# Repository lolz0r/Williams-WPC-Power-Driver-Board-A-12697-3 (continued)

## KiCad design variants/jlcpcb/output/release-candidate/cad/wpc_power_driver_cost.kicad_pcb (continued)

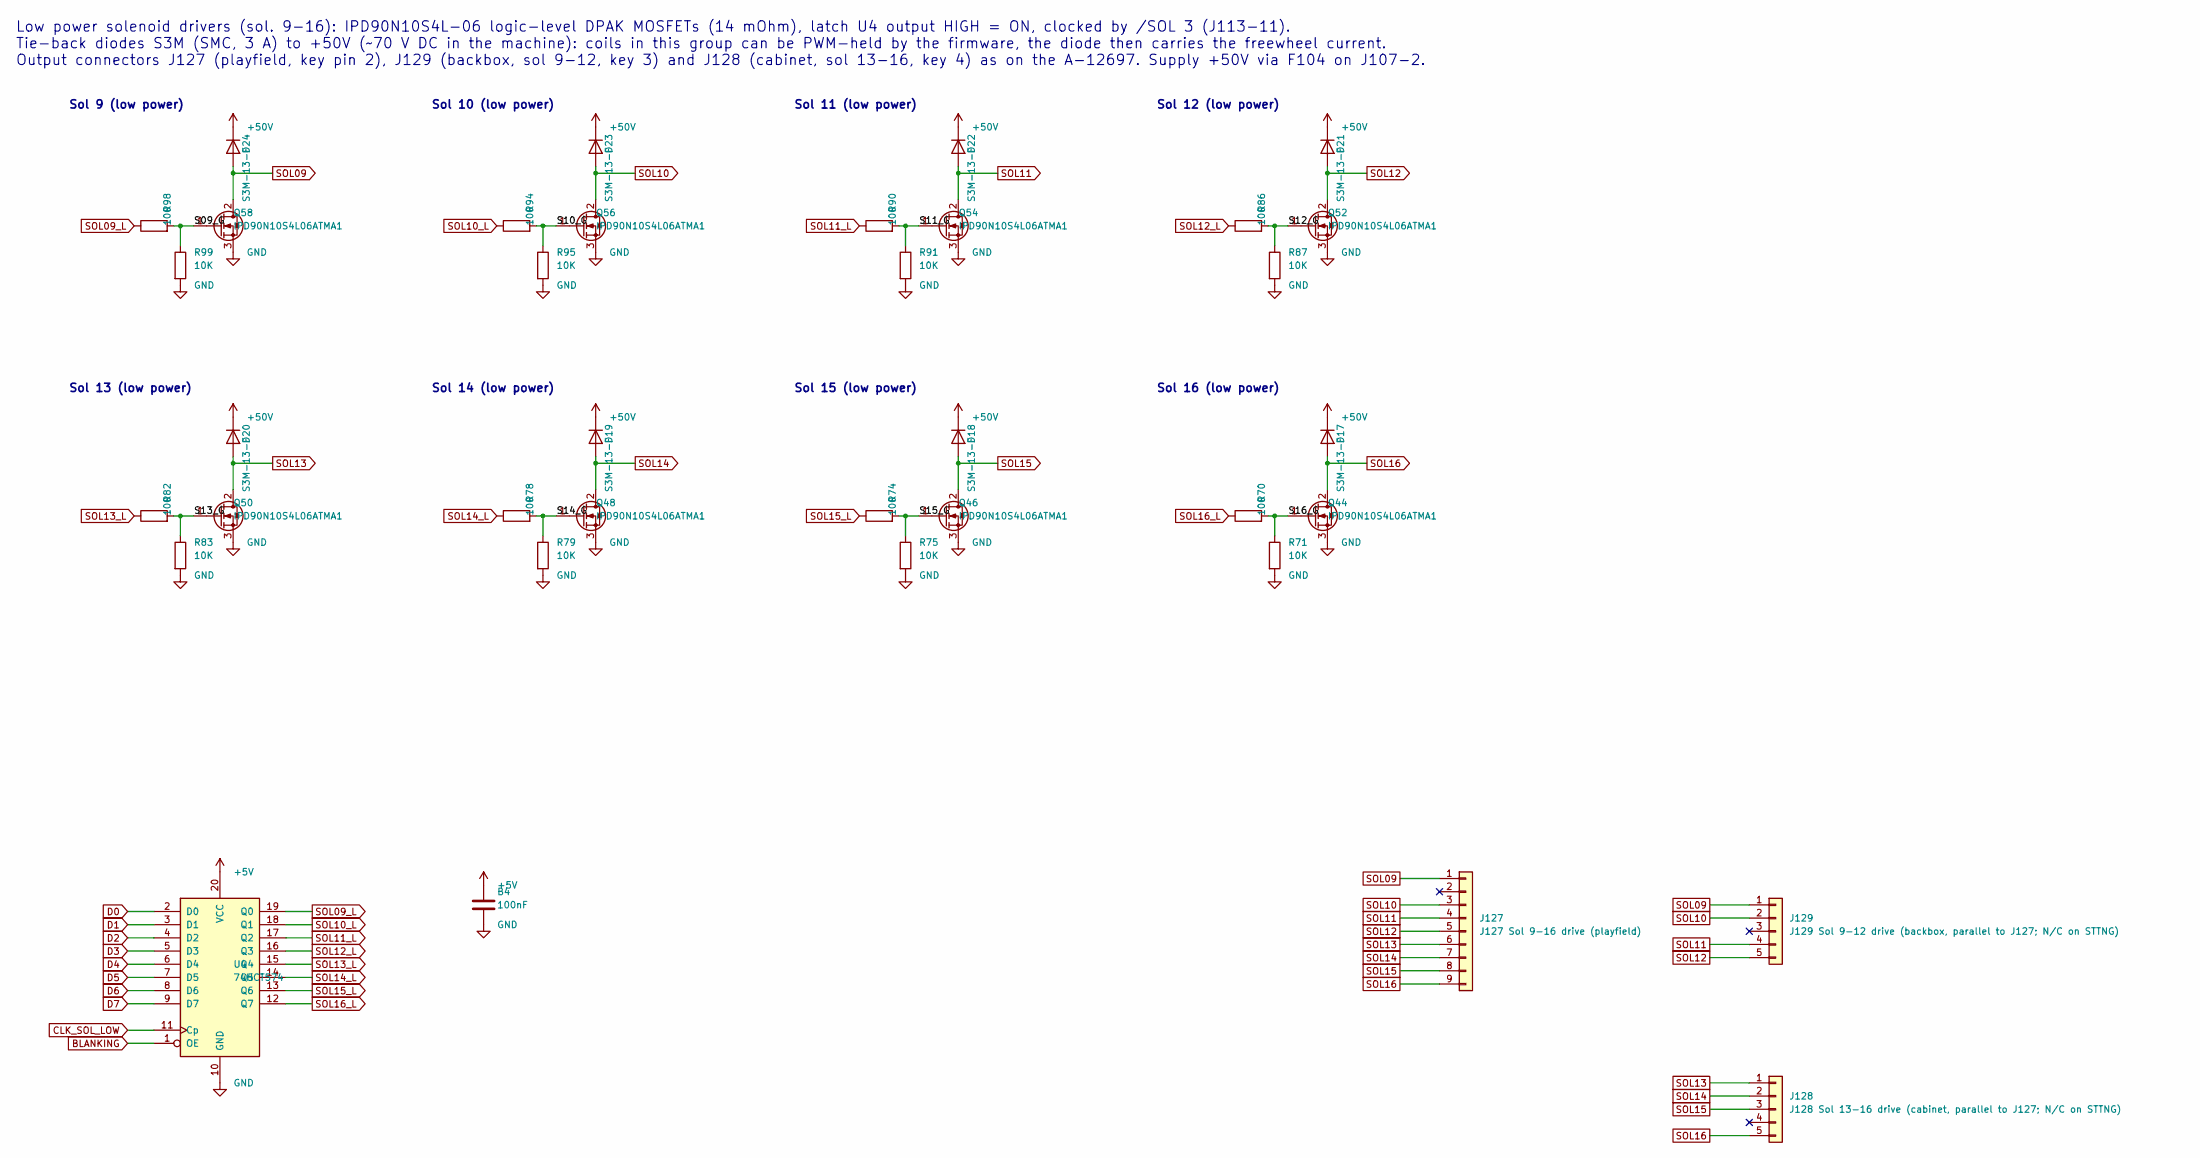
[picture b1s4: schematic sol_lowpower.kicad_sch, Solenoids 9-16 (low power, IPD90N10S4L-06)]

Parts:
B4: 100nF; C_0805_2012Metric; MPN CC0805KRX7R9BB104; JLCPCB Part C49678
D17, D18, D19, D20, D21, D22, D23, D24: S3M-13-F; D_SMC; MPN S3M-13-F; JLCPCB Part C460944
J127: J127 Sol 9-16 drive (playfield); Molex_KK-396_A-41791-0009_1x09_P3.96mm_Vertical; MPN 0026604090; JLCPCB Part C17420444
J128: J128 Sol 13-16 drive (cabinet, parallel to J127; 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; Molex_KK-396_A-41791-0005_1x05_P3.96mm_Vertical; MPN 26604050; JLCPCB Part C505166
J129: J129 Sol 9-12 drive (backbox, parallel to J127; N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; Molex_KK-396_A-41791-0005_1x05_P3.96mm_Vertical; MPN 26604050; JLCPCB Part C505166
Q44, Q46, Q48, Q50, Q52, Q54, Q56, Q58: IPD90N10S4L06ATMA1; TO-252-2; MPN IPD90N10S4L06ATMA1; JLCPCB Part C5440942
R70, R74, R78, R82, R86, R90, R94, R98: 100; R_0805_2012Metric; MPN 0805W8F1000T5E; JLCPCB Part C17408
R71, R75, R79, R83, R87, R91, R95, R99: 10K; R_0805_2012Metric; MPN 0805W8F1002T5E; JLCPCB Part C17414
U4: 74HCT574; SOIC-20W_7.5x12.8mm_P1.27mm; MPN SN74HCT574DWR; JLCPCB Part C6788

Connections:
+5V: B4.1, U4.20 (VCC); also elsewhere on the board
+50V: D17.1 (K), D18.1 (K), D19.1 (K), D20.1 (K), D21.1 (K), D22.1 (K), D23.1 (K), D24.1 (K); also elsewhere on the board
/Sol_LowPower/S09_G: Q58.1 (G), R98.2, R99.1
/Sol_LowPower/S10_G: Q56.1 (G), R94.2, R95.1
/Sol_LowPower/S11_G: Q54.1 (G), R90.2, R91.1
/Sol_LowPower/S12_G: Q52.1 (G), R86.2, R87.1
/Sol_LowPower/S13_G: Q50.1 (G), R82.2, R83.1
/Sol_LowPower/S14_G: Q48.1 (G), R78.2, R79.1
/Sol_LowPower/S15_G: Q46.1 (G), R74.2, R75.1
/Sol_LowPower/S16_G: Q44.1 (G), R70.2, R71.1
BLANKING: U4.1 (OE); also elsewhere on the board
CLK_SOL_LOW: U4.11 (Cp); also elsewhere on the board
D0: U4.2 (D0); also elsewhere on the board
D1: U4.3 (D1); also elsewhere on the board
D2: U4.4 (D2); also elsewhere on the board
D3: U4.5 (D3); also elsewhere on the board
D4: U4.6 (D4); also elsewhere on the board
D5: U4.7 (D5); also elsewhere on the board
D6: U4.8 (D6); also elsewhere on the board
D7: U4.9 (D7); also elsewhere on the board
SOL09: D24.2 (A), J127.1, J129.1, Q58.2 (D)
SOL09_L: R98.1, U4.19 (Q0)
SOL10: D23.2 (A), J127.3, J129.2, Q56.2 (D)
SOL10_L: R94.1, U4.18 (Q1)
SOL11: D22.2 (A), J127.4, J129.4, Q54.2 (D)
SOL11_L: R90.1, U4.17 (Q2)
SOL12: D21.2 (A), J127.5, J129.5, Q52.2 (D)
SOL12_L: R86.1, U4.16 (Q3)
SOL13: D20.2 (A), J127.6, J128.1, Q50.2 (D)
SOL13_L: R82.1, U4.15 (Q4)
SOL14: D19.2 (A), J127.7, J128.2, Q48.2 (D)
SOL14_L: R78.1, U4.14 (Q5)
SOL15: D18.2 (A), J127.8, J128.3, Q46.2 (D)
SOL15_L: R74.1, U4.13 (Q6)
SOL16: D17.2 (A), J127.9, J128.5, Q44.2 (D)
SOL16_L: R70.1, U4.12 (Q7)

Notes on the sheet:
Sol 9 (low power)
Sol 10 (low power)
Sol 11 (low power)
Sol 12 (low power)
Sol 13 (low power)
Sol 14 (low power)
Sol 15 (low power)
Sol 16 (low power)
Low power solenoid drivers (sol. 9-16): IPD90N10S4L-06 logic-level DPAK MOSFETs (14 mOhm), latch U4 output HIGH = ON, clocked by /SOL 3 (J113-11). Tie-back diodes S3M (SMC, 3 A) to +50V (~70 V DC in the machine): coils in this group can be PWM-held by the firmware, the diode then carries the freewh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

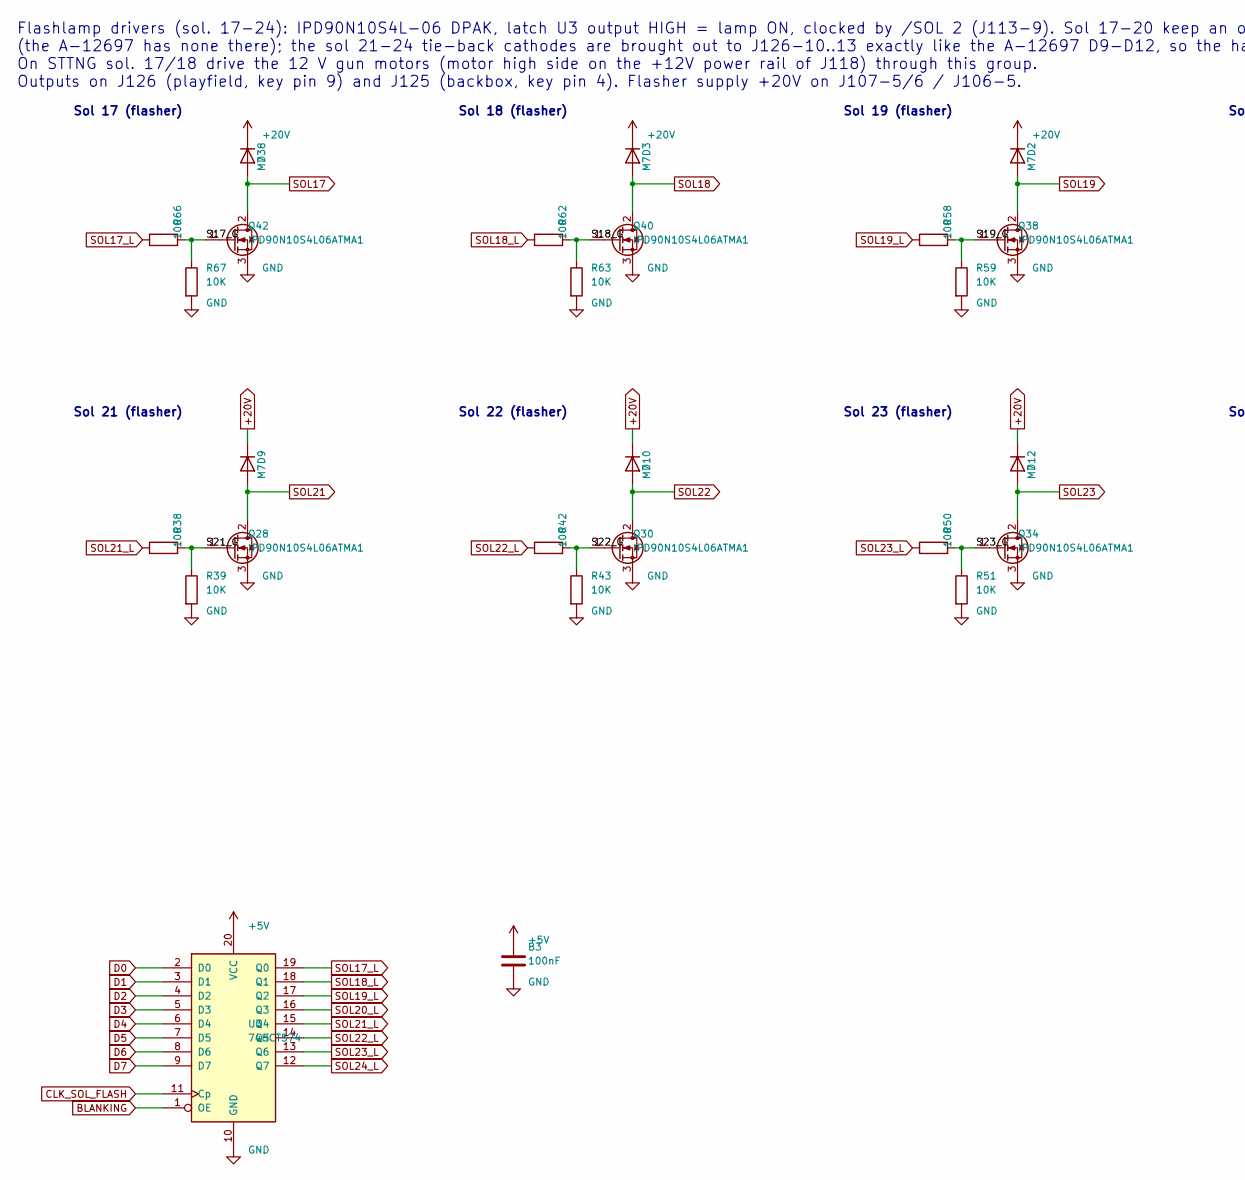
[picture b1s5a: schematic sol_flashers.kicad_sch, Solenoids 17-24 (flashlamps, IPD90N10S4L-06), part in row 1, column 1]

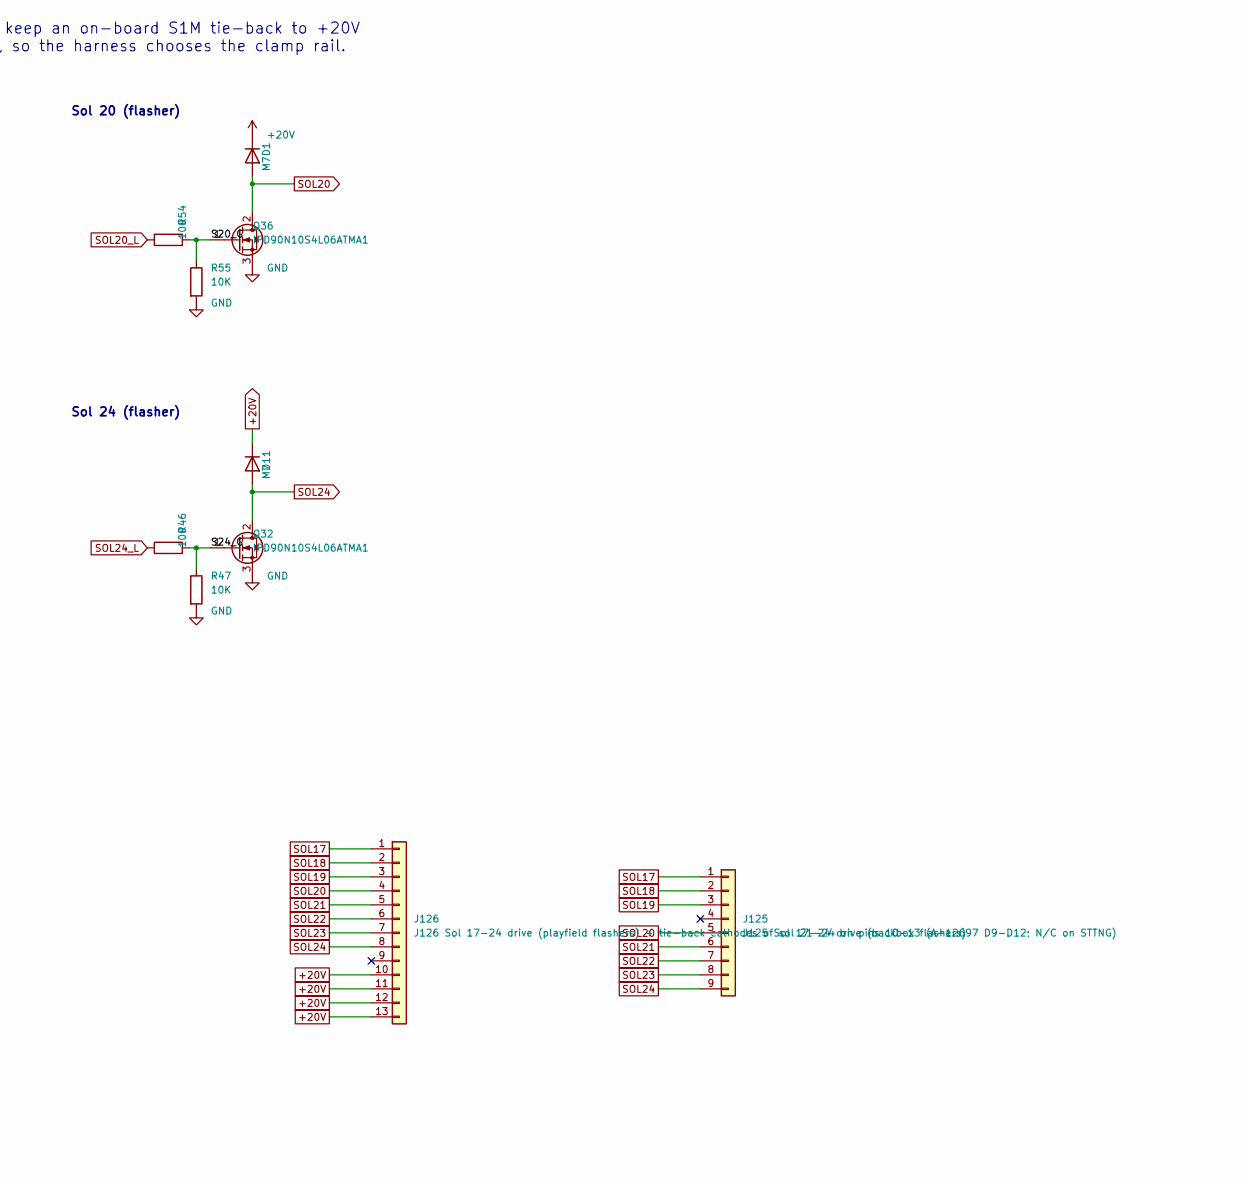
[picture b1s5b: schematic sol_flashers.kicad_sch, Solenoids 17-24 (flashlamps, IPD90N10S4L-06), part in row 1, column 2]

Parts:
B3: 100nF; C_0805_2012Metric; MPN CC0805KRX7R9BB104; JLCPCB Part C49678
D1, D2, D3, D9, D10, D11, D12, D38: M7; D_SMA; MPN M7; JLCPCB Part C95872
J125: J125 Sol 17-24 drive (backbox flashers); Molex_KK-396_A-41791-0009_1x09_P3.96mm_Vertical; MPN 0026604090; JLCPCB Part C17420444
J126: J126 Sol 17-24 drive (playfield flashers) + tie-b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; Molex_KK-396_A-41791-0013_1x13_P3.96mm_Vertical; MPN 0026604130; JLCPCB Part C17226055
Q28, Q30, Q32, Q34, Q36, Q38, Q40, Q42: IPD90N10S4L06ATMA1; TO-252-2; MPN IPD90N10S4L06ATMA1; JLCPCB Part C5440942
R38, R42, R46, R50, R54, R58, R62, R66: 100; R_0805_2012Metric; MPN 0805W8F1000T5E; JLCPCB Part C17408
R39, R43, R47, R51, R55, R59, R63, R67: 10K; R_0805_2012Metric; MPN 0805W8F1002T5E; JLCPCB Part C17414
U3: 74HCT574; SOIC-20W_7.5x12.8mm_P1.27mm; MPN SN74HCT574DWR; JLCPCB Part C6788

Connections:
+5V: B3.1, U3.20 (VCC); also elsewhere on the board
+20V: D1.1 (K), D2.1 (K), D3.1 (K), D9.1 (K), D10.1 (K), D11.1 (K), D12.1 (K), D38.1 (K), J126.10, J126.11, J126.12, J126.13; also elsewhere on the board
/Sol_Flashers/S17_G: Q42.1 (G), R66.2, R67.1
/Sol_Flashers/S18_G: Q40.1 (G), R62.2, R63.1
/Sol_Flashers/S19_G: Q38.1 (G), R58.2, R59.1
/Sol_Flashers/S20_G: Q36.1 (G), R54.2, R55.1
/Sol_Flashers/S21_G: Q28.1 (G), R38.2, R39.1
/Sol_Flashers/S22_G: Q30.1 (G), R42.2, R43.1
/Sol_Flashers/S23_G: Q34.1 (G), R50.2, R51.1
/Sol_Flashers/S24_G: Q32.1 (G), R46.2, R47.1
BLANKING: U3.1 (OE); also elsewhere on the board
CLK_SOL_FLASH: U3.11 (Cp); also elsewhere on the board
D0: U3.2 (D0); also elsewhere on the board
D1: U3.3 (D1); also elsewhere on the board
D2: U3.4 (D2); also elsewhere on the board
D3: U3.5 (D3); also elsewhere on the board
D4: U3.6 (D4); also elsewhere on the board
D5: U3.7 (D5); also elsewhere on the board
D6: U3.8 (D6); also elsewhere on the board
D7: U3.9 (D7); also elsewhere on the board
SOL17: D38.2 (A), J125.1, J126.1, Q42.2 (D)
SOL17_L: R66.1, U3.19 (Q0)
SOL18: D3.2 (A), J125.2, J126.2, Q40.2 (D)
SOL18_L: R62.1, U3.18 (Q1)
SOL19: D2.2 (A), J125.3, J126.3, Q38.2 (D)
SOL19_L: R58.1, U3.17 (Q2)
SOL20: D1.2 (A), J125.5, J126.4, Q36.2 (D)
SOL20_L: R54.1, U3.16 (Q3)
SOL21: D9.2 (A), J125.6, J126.5, Q28.2 (D)
SOL21_L: R38.1, U3.15 (Q4)
SOL22: D10.2 (A), J125.7, J126.6, Q30.2 (D)
SOL22_L: R42.1, U3.14 (Q5)
SOL23: D12.2 (A), J125.8, J126.7, Q34.2 (D)
SOL23_L: R50.1, U3.13 (Q6)
SOL24: D11.2 (A), J125.9, J126.8, Q32.2 (D)
SOL24_L: R46.1, U3.12 (Q7)

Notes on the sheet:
Sol 17 (flasher)
Sol 18 (flasher)
Sol 19 (flasher)
Sol 20 (flasher)
Sol 21 (flasher)
Sol 22 (flasher)
Sol 23 (flasher)
Sol 24 (flasher)
Flashlamp drivers (sol. 17-24): IPD90N10S4L-06 DPAK, latch U3 output HIGH = lamp ON, clocked by /SOL 2 (J113-9). Sol 17-20 keep an on-board S1M tie-back to +20V (the A-12697 has none there); the sol 21-24 tie-back cathodes are brought out to J126-10..13 exactly like the A-12697 D9-D12, so the harne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

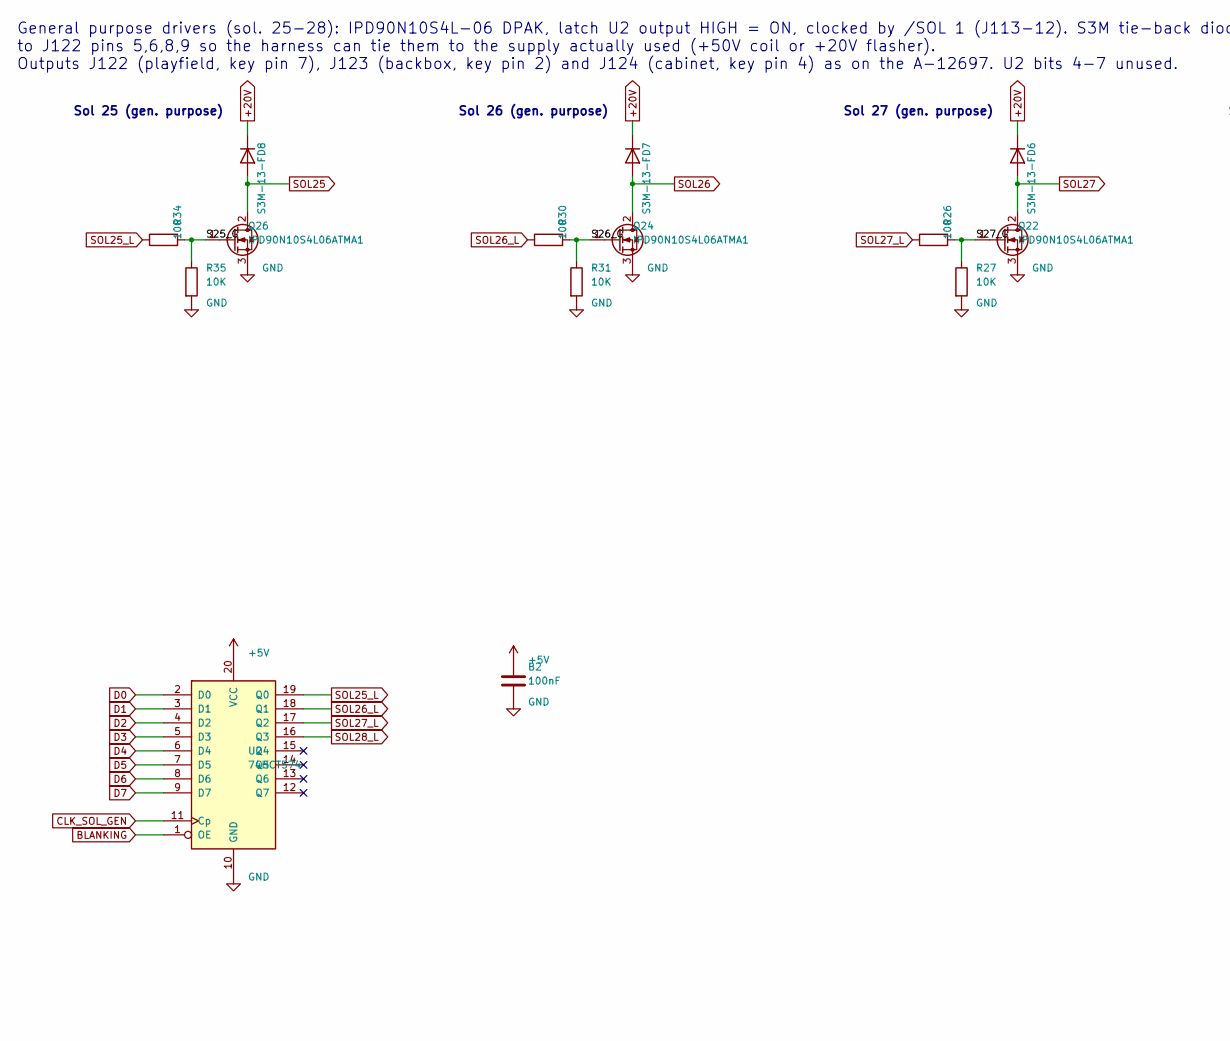
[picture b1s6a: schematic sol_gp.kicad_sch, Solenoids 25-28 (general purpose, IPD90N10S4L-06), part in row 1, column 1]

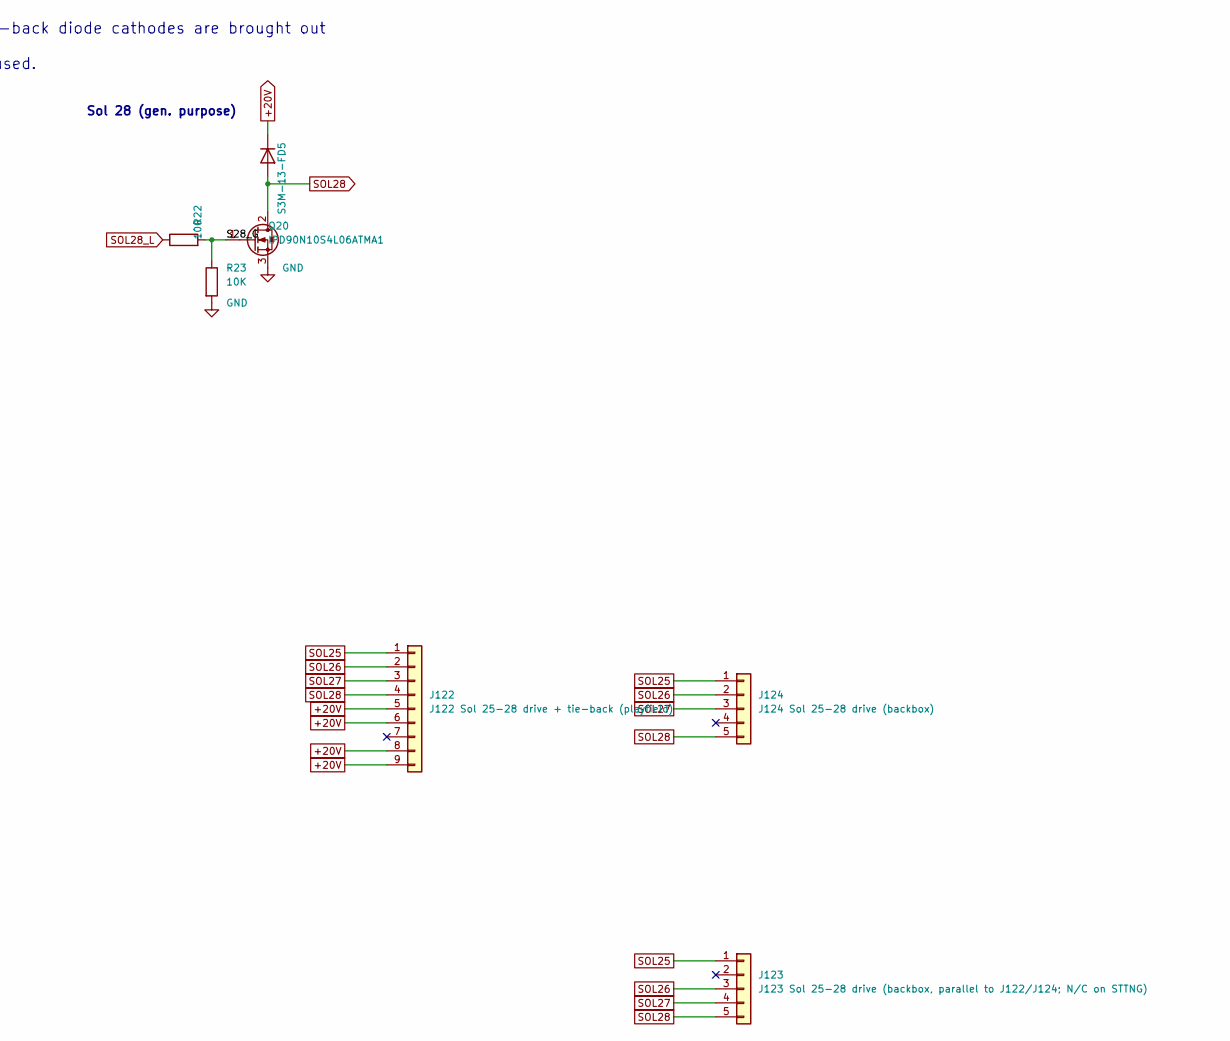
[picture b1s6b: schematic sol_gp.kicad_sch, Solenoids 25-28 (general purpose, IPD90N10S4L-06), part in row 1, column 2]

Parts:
B2: 100nF; C_0805_2012Metric; MPN CC0805KRX7R9BB104; JLCPCB Part C49678
D5, D6, D7, D8: S3M-13-F; D_SMC; MPN S3M-13-F; JLCPCB Part C460944
J122: J122 Sol 25-28 drive + tie-back (playfield); Molex_KK-396_A-41791-0009_1x09_P3.96mm_Vertical; MPN 0026604090; JLCPCB Part C17420444
J123: J123 Sol 25-28 drive (backbox, parallel to J122/J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; Molex_KK-396_A-41791-0005_1x05_P3.96mm_Vertical; MPN 26604050; JLCPCB Part C505166
J124: J124 Sol 25-28 drive (backbox); Molex_KK-396_A-41791-0005_1x05_P3.96mm_Vertical; MPN 26604050; JLCPCB Part C505166
Q20, Q22, Q24, Q26: IPD90N10S4L06ATMA1; TO-252-2; MPN IPD90N10S4L06ATMA1; JLCPCB Part C5440942
R22, R26, R30, R34: 100; R_0805_2012Metric; MPN 0805W8F1000T5E; JLCPCB Part C17408
R23, R27, R31, R35: 10K; R_0805_2012Metric; MPN 0805W8F1002T5E; JLCPCB Part C17414
U2: 74HCT574; SOIC-20W_7.5x12.8mm_P1.27mm; MPN SN74HCT574DWR; JLCPCB Part C6788

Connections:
+5V: B2.1, U2.20 (VCC); also elsewhere on the board
+20V: D5.1 (K), D6.1 (K), D7.1 (K), D8.1 (K), J122.5, J122.6, J122.8, J122.9; also elsewhere on the board
/Sol_GeneralPurpose/S25_G: Q26.1 (G), R34.2, R35.1
/Sol_GeneralPurpose/S26_G: Q24.1 (G), R30.2, R31.1
/Sol_GeneralPurpose/S27_G: Q22.1 (G), R26.2, R27.1
/Sol_GeneralPurpose/S28_G: Q20.1 (G), R22.2, R23.1
BLANKING: U2.1 (OE); also elsewhere on the board
CLK_SOL_GEN: U2.11 (Cp); also elsewhere on the board
D0: U2.2 (D0); also elsewhere on the board
D1: U2.3 (D1); also elsewhere on the board
D2: U2.4 (D2); also elsewhere on the board
D3: U2.5 (D3); also elsewhere on the board
D4: U2.6 (D4); also elsewhere on the board
D5: U2.7 (D5); also elsewhere on the board
D6: U2.8 (D6); also elsewhere on the board
D7: U2.9 (D7); also elsewhere on the board
SOL25: D8.2 (A), J122.1, J123.1, J124.1, Q26.2 (D)
SOL25_L: R34.1, U2.19 (Q0)
SOL26: D7.2 (A), J122.2, J123.3, J124.2, Q24.2 (D)
SOL26_L: R30.1, U2.18 (Q1)
SOL27: D6.2 (A), J122.3, J123.4, J124.3, Q22.2 (D)
SOL27_L: R26.1, U2.17 (Q2)
SOL28: D5.2 (A), J122.4, J123.5, J124.5, Q20.2 (D)
SOL28_L: R22.1, U2.16 (Q3)

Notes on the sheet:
Sol 25 (gen. purpose)
Sol 26 (gen. purpose)
Sol 27 (gen. purpose)
Sol 28 (gen. purpose)
General purpose drivers (sol. 25-28): IPD90N10S4L-06 DPAK, latch U2 output HIGH = ON, clocked by /SOL 1 (J113-12). S3M tie-back diode cathodes are brought out to J122 pins 5,6,8,9 so the harness can tie them to the supply actually used (+50V coil or +20V flasher). Outputs J122 (playfield, key pin 7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

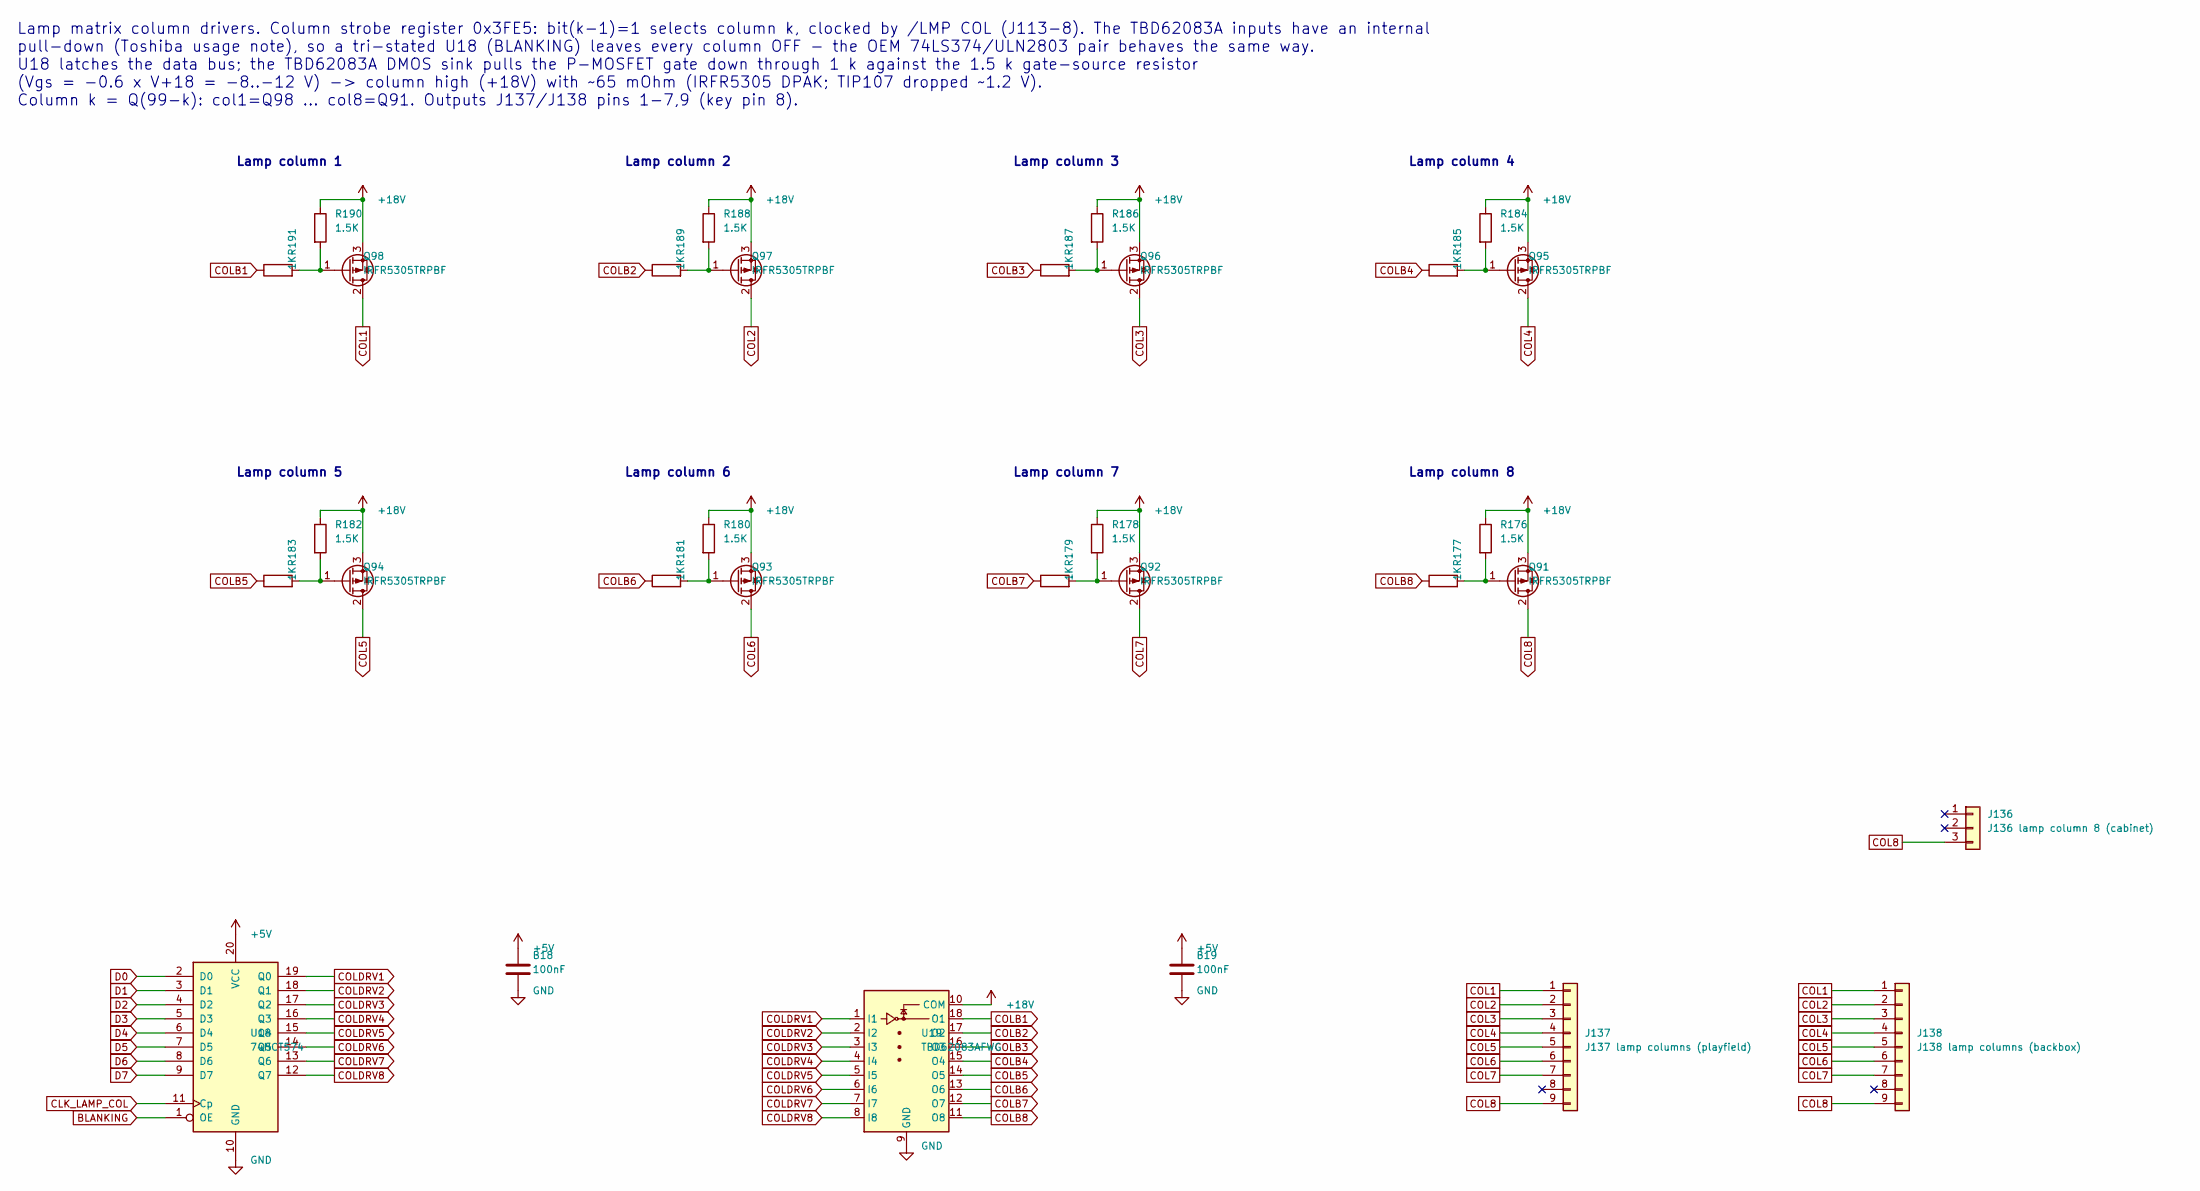
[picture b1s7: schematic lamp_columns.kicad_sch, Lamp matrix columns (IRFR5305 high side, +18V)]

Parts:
B18, B19: 100nF; C_0805_2012Metric; MPN CC0805KRX7R9BB104; JLCPCB Part C49678
J136: J136 lamp column 8 (cabinet); Molex_KK-396_A-41791-0003_1x03_P3.96mm_Vertical; MPN 26604030; JLCPCB Part C240823
J137: J137 lamp columns (playfield); Molex_KK-396_A-41791-0009_1x09_P3.96mm_Vertical; MPN 0026604090; JLCPCB Part C17420444
J138: J138 lamp columns (backbox); Molex_KK-396_A-41791-0009_1x09_P3.96mm_Vertical; MPN 0026604090; JLCPCB Part C17420444
Q91, Q92, Q93, Q94, Q95, Q96, Q97, Q98: IRFR5305TRPBF; TO-252-2; MPN IRFR5305TRPBF; JLCPCB Part C2624
R176, R178, R180, R182, R184, R186, R188, R190: 1.5K; R_0805_2012Metric; MPN 0805W8F1501T5E; JLCPCB Part C4310
R177, R179, R181, R183, R185, R187, R189, R191: 1K; R_0805_2012Metric; MPN 0805W8F1001T5E; JLCPCB Part C17513
U18: 74HCT574; SOIC-20W_7.5x12.8mm_P1.27mm; MPN SN74HCT574DWR; JLCPCB Part C6788
U19: TBD62083AFWG; SOIC-18W_7.5x11.6mm_P1.27mm; MPN TBD62083AFWG,EL; JLCPCB Part C165895

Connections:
+5V: B18.1, B19.1, U18.20 (VCC); also elsewhere on the board
+18V: Q91.3 (S), Q92.3 (S), Q93.3 (S), Q94.3 (S), Q95.3 (S), Q96.3 (S), Q97.3 (S), Q98.3 (S), R176.1, R178.1, R180.1, R182.1, R184.1, R186.1, R188.1, R190.1, U19.10 (COM); also elsewhere on the board
BLANKING: U18.1 (OE); also elsewhere on the board
CLK_LAMP_COL: U18.11 (Cp); also elsewhere on the board
COL1: J137.1, J138.1, Q98.2 (D)
COL2: J137.2, J138.2, Q97.2 (D)
COL3: J137.3, J138.3, Q96.2 (D)
COL4: J137.4, J138.4, Q95.2 (D)
COL5: J137.5, J138.5, Q94.2 (D)
COL6: J137.6, J138.6, Q93.2 (D)
COL7: J137.7, J138.7, Q92.2 (D)
COL8: J136.3, J137.9, J138.9, Q91.2 (D)
COLB1: R191.1, U19.18 (O1)
COLB2: R189.1, U19.17 (O2)
COLB3: R187.1, U19.16 (O3)
COLB4: R185.1, U19.15 (O4)
COLB5: R183.1, U19.14 (O5)
COLB6: R181.1, U19.13 (O6)
COLB7: R179.1, U19.12 (O7)
COLB8: R177.1, U19.11 (O8)
COLDRV1: U18.19 (Q0), U19.1 (I1)
COLDRV2: U18.18 (Q1), U19.2 (I2)
COLDRV3: U18.17 (Q2), U19.3 (I3)
COLDRV4: U18.16 (Q3), U19.4 (I4)
COLDRV5: U18.15 (Q4), U19.5 (I5)
COLDRV6: U18.14 (Q5), U19.6 (I6)
COLDRV7: U18.13 (Q6), U19.7 (I7)
COLDRV8: U18.12 (Q7), U19.8 (I8)
D0: U18.2 (D0); also elsewhere on the board
D1: U18.3 (D1); also elsewhere on the board
D2: U18.4 (D2); also elsewhere on the board
D3: U18.5 (D3); also elsewhere on the board
D4: U18.6 (D4); also elsewhere on the board
D5: U18.7 (D5); also elsewhere on the board
D6: U18.8 (D6); also elsewhere on the board
D7: U18.9 (D7); also elsewhere on the board
unnamed: Q91.1 (G), R176.2, R177.2
unnamed: Q92.1 (G), R178.2, R179.2
unnamed: Q93.1 (G), R180.2, R181.2
unnamed: Q94.1 (G), R182.2, R183.2
unnamed: Q95.1 (G), R184.2, R185.2
unnamed: Q96.1 (G), R186.2, R187.2
unnamed: Q97.1 (G), R188.2, R189.2
unnamed: Q98.1 (G), R190.2, R191.2

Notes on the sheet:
Lamp column 1
Lamp column 2
Lamp column 3
Lamp column 4
Lamp column 5
Lamp column 6
Lamp column 7
Lamp column 8
Lamp matrix column drivers. Column strobe register 0x3FE5: bit(k-1)=1 selects column k, clocked by /LMP COL (J113-8). The TBD62083A inputs have an internal pull-down (Toshiba usage note), so a tri-stated U18 (BLANKING) leaves every column OFF - the OEM 74LS374/ULN2803 pair behaves the same way. U18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
